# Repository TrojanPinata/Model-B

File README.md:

<div align="center">

# Model-B

### A 75% keyboard based on the RP2040 MCU with hotswappable switches, OLED display, and rotary encoder.

The Model-B is the second keyboard I've developed and aims to be the direct successor to the [Model-K](https://github.com/TrojanPinata/Model-K-Pico). I made this with the intention to develop a hotswappable keyboard which uses SMD components in order to reduce soldering overhead and learn microcontroller hardware development. The case is clear acrylic with a delrin switchplate and holds a eleven degree angle, and is reasonably heavy - a much more complete feel compared to the Model-K. 

See [what_is_this.md](what_is_this.md) for some info regarding why I made this and some of the specifics for getting setup.

## Features

<div align="left">

* 75% layout
* Hotswappable switches
* Primarily SMD PCB
* Completely laster cut housing
* 128x32 OLED display
* Chip viewing window

</div>

### Photography by [Kobe Brian!](https://www.kobebrian.com/)

</div>

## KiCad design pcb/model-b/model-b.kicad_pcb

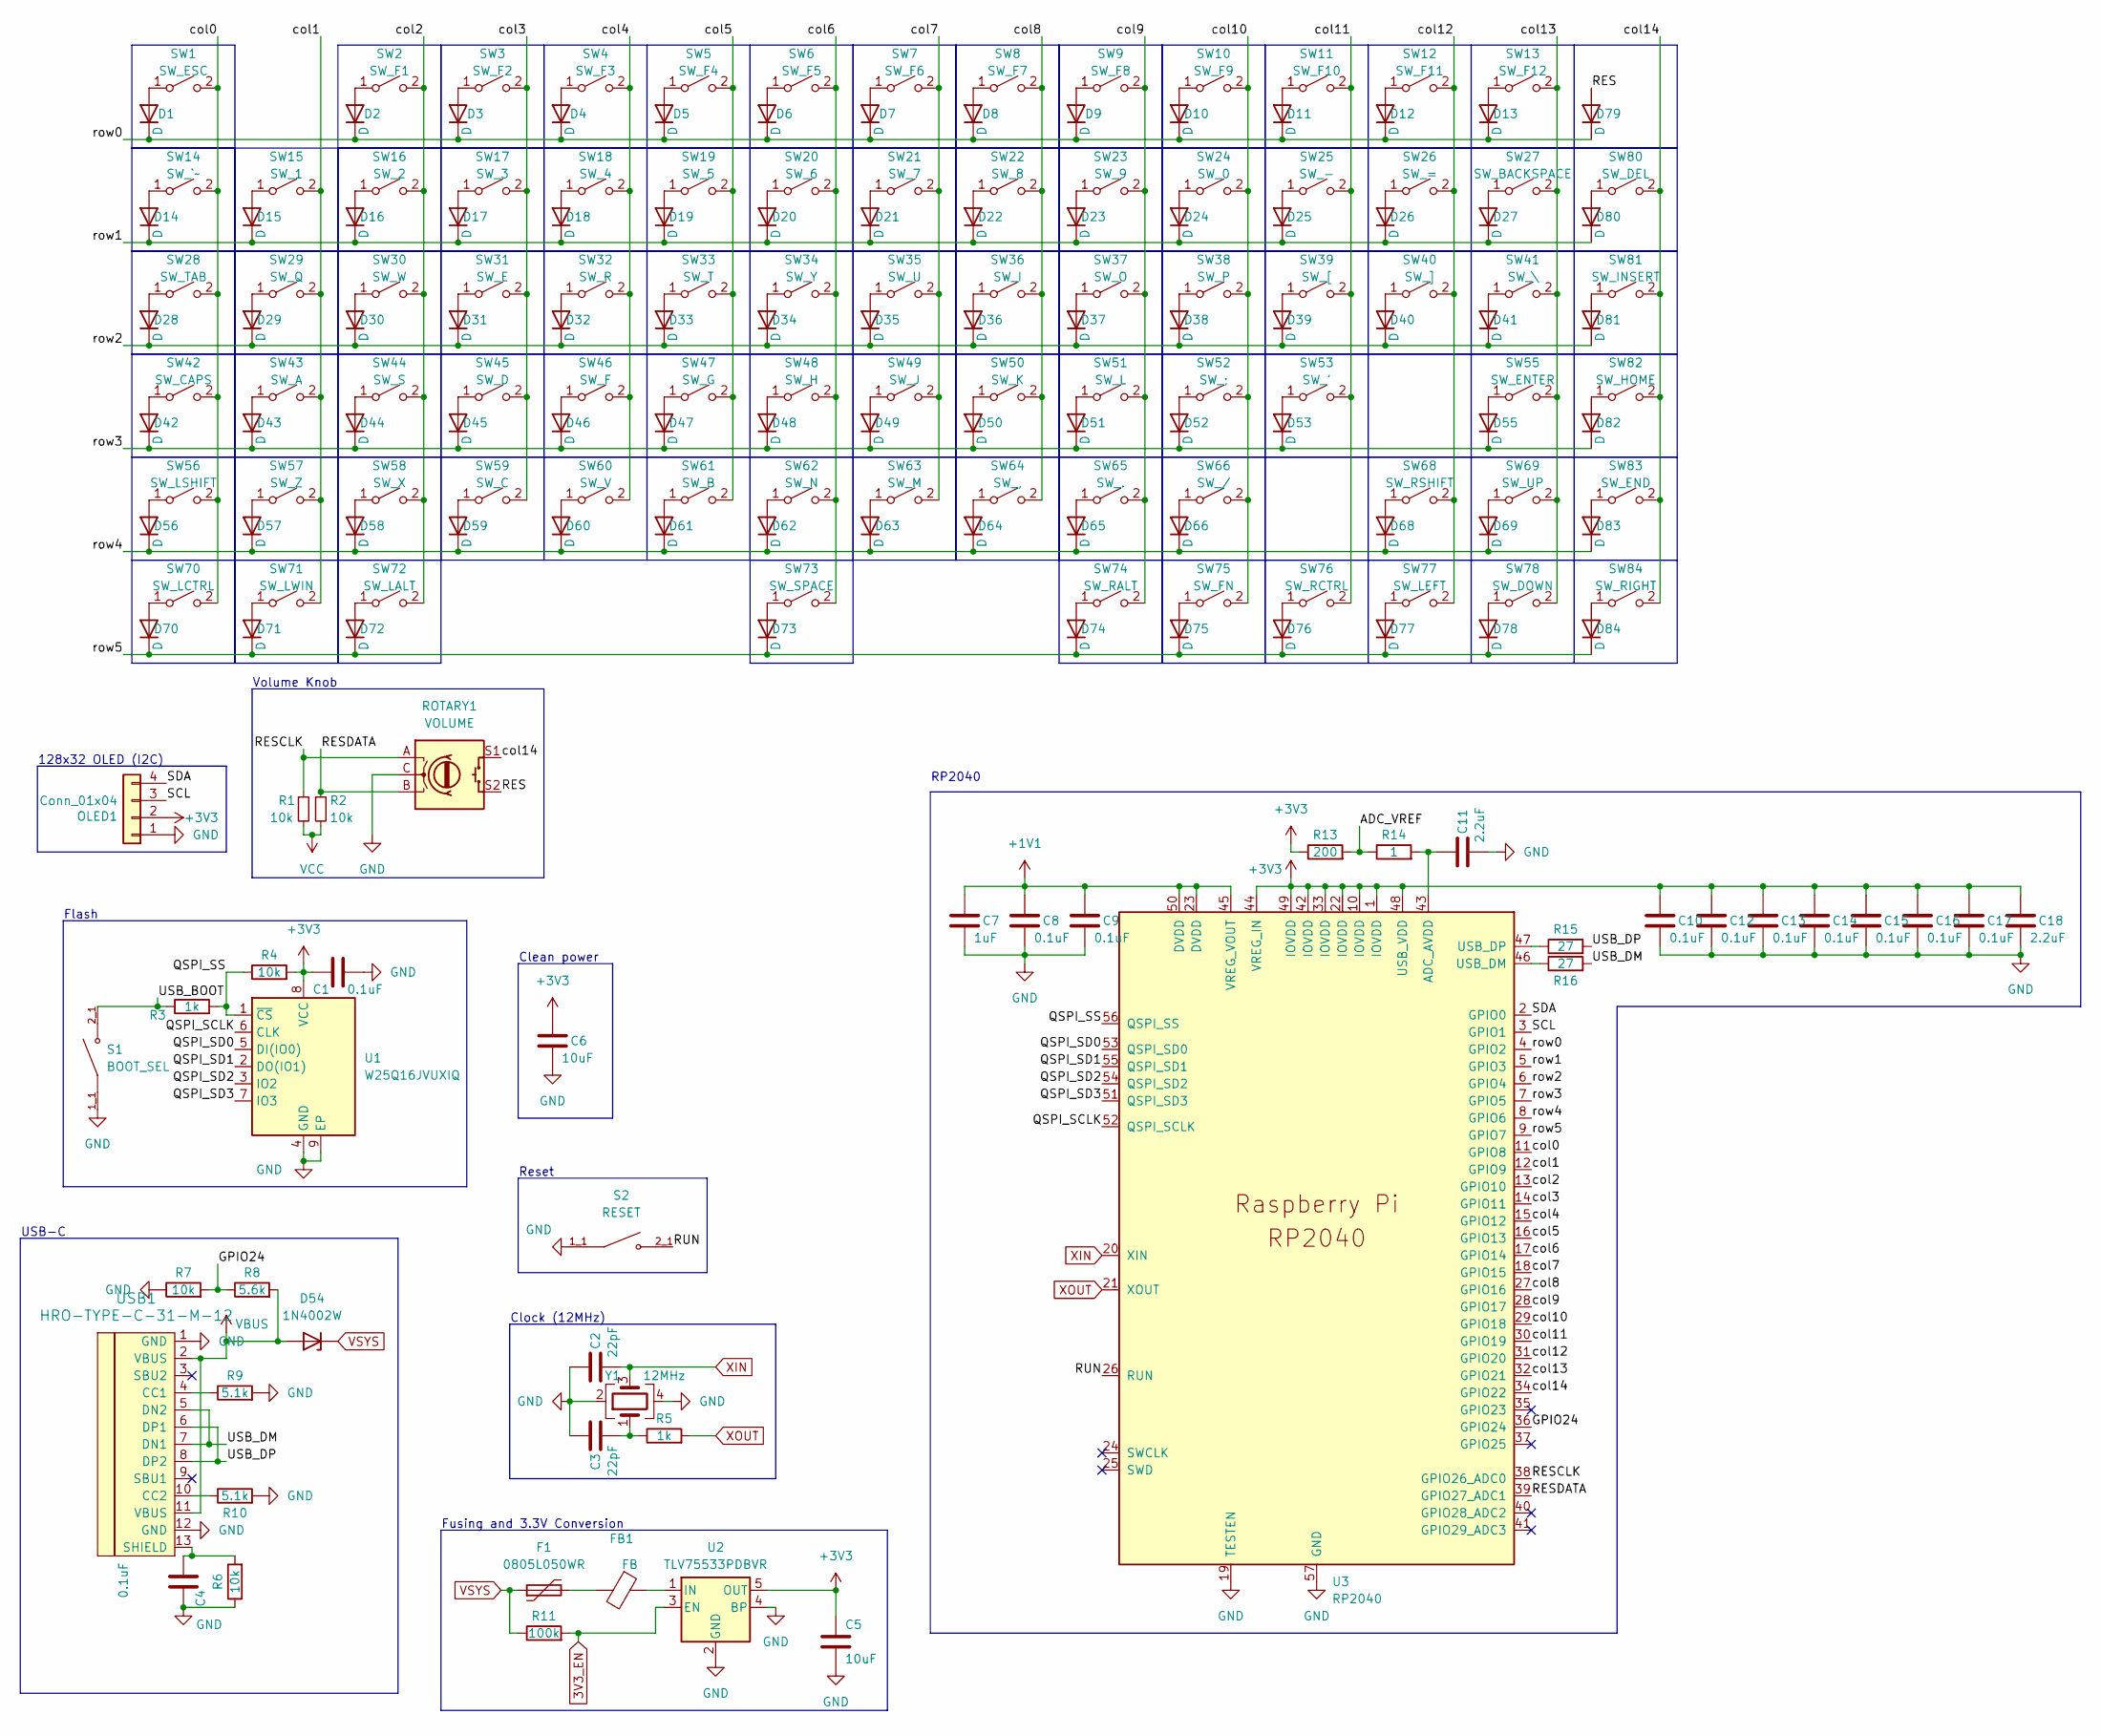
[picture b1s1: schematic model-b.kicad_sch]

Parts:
C1, C4, C8, C9, C10, C12, C13, C14, C15, C16, C17: 0.1uF; C_0402_1005Metric
C2, C3: 22pF; C_0402_1005Metric
C5, C6: 10uF; C_0402_1005Metric
C7: 1uF; C_0402_1005Metric
C11, C18: 2.2uF; C_0402_1005Metric
D1, D2, D3, D4, D5, D6, D7, D8, D9, D10, D11, D12, D13, D14, D15, D16, D17, D18, D19, D20, D21, D22, D23, D24, D25, D26, D27, D28, D29, D30, D31, D32, D33, D34, D35, D36, D37, D38, D39, D40, D41, D42, D43, D44, D45, D46, D47, D48, D49, D50, D51, D52, D53, D55, D56, D57, D58, D59, D60, D61, D62, D63, D64, D65, D66, D68, D69, D70, D71, D72, D73, D74, D75, D76, D77, D78, D79, D80, D81, D82, D83, D84: D; D_0402_1005Metric
D54: 1N4002W; D_SOD-123
F1: 0805L050WR; Fuse_0805_2012Metric
FB1: FB; R_0402_1005Metric
OLED1: Conn_01x04; PinSocket_1x04_P2.54mm_Vertical
R1, R2, R4, R6, R7: 10k; R_0402_1005Metric
R3, R5: 1k; R_0402_1005Metric
R8: 5.6k; R_0402_1005Metric
R9, R10: 5.1k; R_0402_1005Metric
R11: 100k; R_0402_1005Metric
R13: 200; R_0402_1005Metric
R14: 1; R_0402_1005Metric
R15, R16: 27; R_0402_1005Metric
ROTARY1: VOLUME; RotaryEncoder_Alps_EC11E-Switch_Vertical_H20mm_CircularMoun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
S1: BOOT_SEL; SW_EVQ-P7A01P; PARTREV 2022.4
S2: RESET; SW_EVQ-P7A01P; PARTREV 2022.4
SW1: SW_ESC; MXOnly-1U-Hotswap
SW2: SW_F1; MXOnly-1U-Hotswap
SW3: SW_F2; MXOnly-1U-Hotswap
SW4: SW_F3; MXOnly-1U-Hotswap
SW5: SW_F4; MXOnly-1U-Hotswap
SW6: SW_F5; MXOnly-1U-Hotswap
SW7: SW_F6; MXOnly-1U-Hotswap
SW8: SW_F7; MXOnly-1U-Hotswap
SW9: SW_F8; MXOnly-1U-Hotswap
SW10: SW_F9; MXOnly-1U-Hotswap
SW11: SW_F10; MXOnly-1U-Hotswap
SW12: SW_F11; MXOnly-1U-Hotswap
SW13: SW_F12; MXOnly-1U-Hotswap
SW14: SW_`~; MXOnly-1U-Hotswap
SW15: SW_1; MXOnly-1U-Hotswap
SW16: SW_2; MXOnly-1U-Hotswap
SW17: SW_3; MXOnly-1U-Hotswap
SW18: SW_4; MXOnly-1U-Hotswap
SW19: SW_5; MXOnly-1U-Hotswap
SW20: SW_6; MXOnly-1U-Hotswap
SW21: SW_7; MXOnly-1U-Hotswap
SW22: SW_8; MXOnly-1U-Hotswap
SW23: SW_9; MXOnly-1U-Hotswap
SW24: SW_0; MXOnly-1U-Hotswap
SW25: SW_-; MXOnly-1U-Hotswap
SW26: SW_=; MXOnly-1U-Hotswap
SW27: SW_BACKSPACE; MXOnly-2U-Hotswap
SW28: SW_TAB; MXOnly-1.5U-Hotswap
SW29: SW_Q; MXOnly-1U-Hotswap
SW30: SW_W; MXOnly-1U-Hotswap
SW31: SW_E; MXOnly-1U-Hotswap
SW32: SW_R; MXOnly-1U-Hotswap
SW33: SW_T; MXOnly-1U-Hotswap
SW34: SW_Y; MXOnly-1U-Hotswap
SW35: SW_U; MXOnly-1U-Hotswap
SW36: SW_I; MXOnly-1U-Hotswap
SW37: SW_O; MXOnly-1U-Hotswap
SW38: SW_P; MXOnly-1U-Hotswap
SW39: SW_[; MXOnly-1U-Hotswap
SW40: SW_]; MXOnly-1U-Hotswap
SW41: SW_\; MXOnly-1.5U-Hotswap
SW42: SW_CAPS; MXOnly-1.75U-Hotswap
SW43: SW_A; MXOnly-1U-Hotswap
SW44: SW_S; MXOnly-1U-Hotswap
SW45: SW_D; MXOnly-1U-Hotswap
SW46: SW_F; MXOnly-1U-Hotswap
SW47: SW_G; MXOnly-1U-Hotswap
SW48: SW_H; MXOnly-1U-Hotswap
SW49: SW_J; MXOnly-1U-Hotswap
SW50: SW_K; MXOnly-1U-Hotswap
SW51: SW_L; MXOnly-1U-Hotswap
SW52: SW_;; MXOnly-1U-Hotswap
SW53: SW_'; MXOnly-1U-Hotswap
SW55: SW_ENTER; MXOnly-2.25U-Hotswap
SW56: SW_LSHIFT; MXOnly-2.25U-Hotswap
SW57: SW_Z; MXOnly-1U-Hotswap
SW58: SW_X; MXOnly-1U-Hotswap
SW59: SW_C; MXOnly-1U-Hotswap
SW60: SW_V; MXOnly-1U-Hotswap
SW61: SW_B; MXOnly-1U-Hotswap
SW62: SW_N; MXOnly-1U-Hotswap
SW63: SW_M; MXOnly-1U-Hotswap
SW64: SW_,; MXOnly-1U-Hotswap
SW65: SW_.; MXOnly-1U-Hotswap
SW66: SW_/; MXOnly-1U-Hotswap
SW68: SW_RSHIFT; MXOnly-1.75U-Hotswap
SW69: SW_UP; MXOnly-1U-Hotswap
SW70: SW_LCTRL; MXOnly-1.25U-Hotswap
SW71: SW_LWIN; MXOnly-1.25U-Hotswap
SW72: SW_LALT; MXOnly-1.25U-Hotswap
SW73: SW_SPACE; MXOnly-6.25U-Hotswap
SW74: SW_RALT; MXOnly-1U-Hotswap
SW75: SW_FN; MXOnly-1U-Hotswap
SW76: SW_RCTRL; MXOnly-1U-Hotswap
SW77: SW_LEFT; MXOnly-1U-Hotswap
SW78: SW_DOWN; MXOnly-1U-Hotswap
SW80: SW_DEL; MXOnly-1U-Hotswap
SW81: SW_INSERT; MXOnly-1U-Hotswap
SW82: SW_HOME; MXOnly-1U-Hotswap
SW83: SW_END; MXOnly-1U-Hotswap
SW84: SW_RIGHT; MXOnly-1U-Hotswap
U1: W25Q16JVUXIQ; SON-8-1EP_3x2mm_P0.5mm_EP1.4x1.6mm
U2: TLV75533PDBVR; SOT-23-5
U3: RP2040; RP2040-QFN-56
USB1: HRO-TYPE-C-31-M-12
Y1: 12MHz; Crystal_SMD_3225-4Pin_3.2x2.5mm

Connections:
3V3_EN: R11.2, U2.3 (EN)
+1V1: C7.1, C8.1, C9.1, U3.23 (DVDD), U3.45 (VREG_VOUT), U3.50 (DVDD)
+3V3: C1.2, C5.1, C6.1, C10.1, C12.1, C13.1, C14.1, C15.1, C16.1, C17.1, C18.1, OLED1.2, R4.2, R13.1, U1.8 (VCC), U2.5 (OUT), U3.1 (IOVDD), U3.10 (IOVDD), U3.22 (IOVDD), U3.33 (IOVDD), U3.42 (IOVDD), U3.44 (VREG_IN), U3.48 (USB_VDD), U3.49 (IOVDD)
/ADC_VREF: R13.2, R14.1
/GPIO24: R7.2, R8.1, U3.36 (GPIO24)
/QSPI_SCLK: U1.6 (CLK), U3.52 (QSPI_SCLK)
/QSPI_SD0: U1.5 (DI(IO0)), U3.53 (QSPI_SD0)
/QSPI_SD1: U1.2 (DO(IO1)), U3.55 (QSPI_SD1)
/QSPI_SD2: U1.3 (IO2), U3.54 (QSPI_SD2)
/QSPI_SD3: U1.7 (IO3), U3.51 (QSPI_SD3)
/QSPI_SS: R3.2, R4.1, U1.1 (~CS), U3.56 (QSPI_SS)
/RES: D79.2 (A), ROTARY1.S2
/RESCLK: R1.1, ROTARY1.A, U3.38 (GPIO26_ADC0)
/RESDATA: R2.1, ROTARY1.B, U3.39 (GPIO27_ADC1)
/RUN: S2.2_1, U3.26 (RUN)
/SCL: OLED1.3, U3.3 (GPIO1)
/SDA: OLED1.4, U3.2 (GPIO0)
/USB_BOOT: R3.1, S1.2_1
/USB_DM: R16.2, USB1.5 (DN2), USB1.7 (DN1)
/USB_DP: R15.2, USB1.6 (DP1), USB1.8 (DP2)
/col0: SW1.2 (B), SW14.2 (B), SW28.2 (B), SW42.2 (B), SW56.2 (B), SW70.2 (B), U3.11 (GPIO8)
/col1: SW15.2 (B), SW29.2 (B), SW43.2 (B), SW57.2 (B), SW71.2 (B), U3.12 (GPIO9)
/col2: SW2.2 (B), SW16.2 (B), SW30.2 (B), SW44.2 (B), SW58.2 (B), SW72.2 (B), U3.13 (GPIO10)
/col3: SW3.2 (B), SW17.2 (B), SW31.2 (B), SW45.2 (B), SW59.2 (B), U3.14 (GPIO11)
/col4: SW4.2 (B), SW18.2 (B), SW32.2 (B), SW46.2 (B), SW60.2 (B), U3.15 (GPIO12)
/col5: SW5.2 (B), SW19.2 (B), SW33.2 (B), SW47.2 (B), SW61.2 (B), U3.16 (GPIO13)
/col6: SW6.2 (B), SW20.2 (B), SW34.2 (B), SW48.2 (B), SW62.2 (B), SW73.2 (B), U3.17 (GPIO14)
/col7: SW7.2 (B), SW21.2 (B), SW35.2 (B), SW49.2 (B), SW63.2 (B), U3.18 (GPIO15)
/col8: SW8.2 (B), SW22.2 (B), SW36.2 (B), SW50.2 (B), SW64.2 (B), U3.27 (GPIO16)
/col9: SW9.2 (B), SW23.2 (B), SW37.2 (B), SW51.2 (B), SW65.2 (B), SW74.2 (B), U3.28 (GPIO17)
/col10: SW10.2 (B), SW24.2 (B), SW38.2 (B), SW52.2 (B), SW66.2 (B), SW75.2 (B), U3.29 (GPIO18)
/col11: SW11.2 (B), SW25.2 (B), SW39.2 (B), SW53.2 (B), SW76.2 (B), U3.30 (GPIO19)
/col12: SW12.2 (B), SW26.2 (B), SW40.2 (B), SW68.2 (B), SW77.2 (B), U3.31 (GPIO20)
/col13: SW13.2 (B), SW27.2 (B), SW41.2 (B), SW55.2 (B), SW69.2 (B), SW78.2 (B), U3.32 (GPIO21)
/col14: ROTARY1.S1, SW80.2 (B), SW81.2 (B), SW82.2 (B), SW83.2 (B), SW84.2 (B), U3.34 (GPIO22)
/row0: D1.1 (K), D2.1 (K), D3.1 (K), D4.1 (K), D5.1 (K), D6.1 (K), D7.1 (K), D8.1 (K), D9.1 (K), D10.1 (K), D11.1 (K), D12.1 (K), D13.1 (K), D79.1 (K), U3.4 (GPIO2)
/row1: D14.1 (K), D15.1 (K), D16.1 (K), D17.1 (K), D18.1 (K), D19.1 (K), D20.1 (K), D21.1 (K), D22.1 (K), D23.1 (K), D24.1 (K), D25.1 (K), D26.1 (K), D27.1 (K), D80.1 (K), U3.5 (GPIO3)
/row2: D28.1 (K), D29.1 (K), D30.1 (K), D31.1 (K), D32.1 (K), D33.1 (K), D34.1 (K), D35.1 (K), D36.1 (K), D37.1 (K), D38.1 (K), D39.1 (K), D40.1 (K), D41.1 (K), D81.1 (K), U3.6 (GPIO4)
/row3: D42.1 (K), D43.1 (K), D44.1 (K), D45.1 (K), D46.1 (K), D47.1 (K), D48.1 (K), D49.1 (K), D50.1 (K), D51.1 (K), D52.1 (K), D53.1 (K), D55.1 (K), D82.1 (K), U3.7 (GPIO5)
/row4: D56.1 (K), D57.1 (K), D58.1 (K), D59.1 (K), D60.1 (K), D61.1 (K), D62.1 (K), D63.1 (K), D64.1 (K), D65.1 (K), D66.1 (K), D68.1 (K), D69.1 (K), D83.1 (K), U3.8 (GPIO6)
/row5: D70.1 (K), D71.1 (K), D72.1 (K), D73.1 (K), D74.1 (K), D75.1 (K), D76.1 (K), D77.1 (K), D78.1 (K), D84.1 (K), U3.9 (GPIO7)
GND: C1.1, C2.1, C3.2, C4.2, C5.2, C6.2, C7.2, C8.2, C9.2, C10.2, C11.2, C12.2, C13.2, C14.2, C15.2, C16.2, C17.2, C18.2, OLED1.1, R6.1, R7.1, R9.2, R10.2, ROTARY1.C, S1.1_1, S2.1_1, U1.4 (GND), U1.9 (EP), U2.2 (GND), U2.4 (BP), U3.19 (TESTEN), U3.57 (GND), USB1.1 (GND), USB1.12 (GND), Y1.2, Y1.4
unnamed: C3.1, R5.1, Y1.1
unnamed: D1.2 (A), SW1.1 (A)
unnamed: D2.2 (A), SW2.1 (A)
unnamed: D3.2 (A), SW3.1 (A)
unnamed: D4.2 (A), SW4.1 (A)
unnamed: D5.2 (A), SW5.1 (A)
unnamed: D6.2 (A), SW6.1 (A)
unnamed: D7.2 (A), SW7.1 (A)
unnamed: D8.2 (A), SW8.1 (A)
unnamed: D9.2 (A), SW9.1 (A)
unnamed: D10.2 (A), SW10.1 (A)
unnamed: D11.2 (A), SW11.1 (A)
unnamed: D12.2 (A), SW12.1 (A)
unnamed: D13.2 (A), SW13.1 (A)
unnamed: D14.2 (A), SW14.1 (A)
unnamed: D15.2 (A), SW15.1 (A)
unnamed: D16.2 (A), SW16.1 (A)
unnamed: D17.2 (A), SW17.1 (A)
unnamed: D18.2 (A), SW18.1 (A)
unnamed: D19.2 (A), SW19.1 (A)
unnamed: D20.2 (A), SW20.1 (A)
unnamed: D21.2 (A), SW21.1 (A)
unnamed: D22.2 (A), SW22.1 (A)
unnamed: D23.2 (A), SW23.1 (A)
unnamed: D24.2 (A), SW24.1 (A)
unnamed: D25.2 (A), SW25.1 (A)
unnamed: D26.2 (A), SW26.1 (A)
unnamed: D27.2 (A), SW27.1 (A)
unnamed: D28.2 (A), SW28.1 (A)
unnamed: D29.2 (A), SW29.1 (A)
unnamed: D30.2 (A), SW30.1 (A)
unnamed: D31.2 (A), SW31.1 (A)
unnamed: D32.2 (A), SW32.1 (A)
unnamed: D33.2 (A), SW33.1 (A)
unnamed: D34.2 (A), SW34.1 (A)
unnamed: D35.2 (A), SW35.1 (A)
unnamed: D36.2 (A), SW36.1 (A)
unnamed: D37.2 (A), SW37.1 (A)
unnamed: D38.2 (A), SW38.1 (A)
unnamed: D39.2 (A), SW39.1 (A)
unnamed: D40.2 (A), SW40.1 (A)
unnamed: D41.2 (A), SW41.1 (A)
unnamed: D42.2 (A), SW42.1 (A)
unnamed: D43.2 (A), SW43.1 (A)
unnamed: D44.2 (A), SW44.1 (A)
unnamed: D45.2 (A), SW45.1 (A)
unnamed: D46.2 (A), SW46.1 (A)
unnamed: D47.2 (A), SW47.1 (A)
unnamed: D48.2 (A), SW48.1 (A)
unnamed: D49.2 (A), SW49.1 (A)
unnamed: D50.2 (A), SW50.1 (A)
unnamed: D51.2 (A), SW51.1 (A)
unnamed: D52.2 (A), SW52.1 (A)
unnamed: D53.2 (A), SW53.1 (A)
unnamed: D55.2 (A), SW55.1 (A)
unnamed: D56.2 (A), SW56.1 (A)
unnamed: D57.2 (A), SW57.1 (A)
unnamed: D58.2 (A), SW58.1 (A)
unnamed: D59.2 (A), SW59.1 (A)
unnamed: D60.2 (A), SW60.1 (A)
unnamed: D61.2 (A), SW61.1 (A)
unnamed: D62.2 (A), SW62.1 (A)
unnamed: D63.2 (A), SW63.1 (A)
unnamed: D64.2 (A), SW64.1 (A)
unnamed: D65.2 (A), SW65.1 (A)
unnamed: D66.2 (A), SW66.1 (A)
unnamed: D68.2 (A), SW68.1 (A)
unnamed: D69.2 (A), SW69.1 (A)
unnamed: D70.2 (A), SW70.1 (A)
unnamed: D71.2 (A), SW71.1 (A)
unnamed: D72.2 (A), SW72.1 (A)
unnamed: D73.2 (A), SW73.1 (A)
unnamed: D74.2 (A), SW74.1 (A)
unnamed: D75.2 (A), SW75.1 (A)
unnamed: D76.2 (A), SW76.1 (A)
unnamed: D77.2 (A), SW77.1 (A)
unnamed: D78.2 (A), SW78.1 (A)
unnamed: D80.2 (A), SW80.1 (A)
unnamed: D81.2 (A), SW81.1 (A)
unnamed: D82.2 (A), SW82.1 (A)
unnamed: D83.2 (A), SW83.1 (A)
unnamed: D84.2 (A), SW84.1 (A)
unnamed: F1.2, FB1.2
unnamed: FB1.1, U2.1 (IN)
unnamed: C11.1, R14.2, U3.43 (ADC_AVDD)
unnamed: R16.1, U3.46 (USB_DM)
unnamed: R15.1, U3.47 (USB_DP)
unnamed: R9.1, USB1.4 (CC1)
unnamed: R10.1, USB1.10 (CC2)
unnamed: C4.1, R6.2, USB1.13 (SHIELD)
VBUS: D54.2 (A), R8.2, USB1.2 (VBUS), USB1.11 (VBUS)
VCC: R1.2, R2.2
VSYS: D54.1 (K), F1.1, R11.1
XIN: C2.2, U3.20 (XIN), Y1.3
XOUT: R5.2, U3.21 (XOUT)

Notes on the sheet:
128x32 OLED (I2C)
Clean power
USB-C
Flash
Fusing and 3.3V Conversion
Volume Knob
Reset
Clock (12MHz)
RP2040

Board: 2 copper layers, 208 parts (0 on the bottom side), 137 nets, no tracks yet.

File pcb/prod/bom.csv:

Designator,Footprint,Quantity,Value,LCSC Part #
"C1, C10, C12, C13, C14, C15, C16, C17, C4, C8, C9",0402,11,0.1uF,C1525
"C11, C18",0402,2,2.2uF,C12530
"C2, C3",0402,2,20pF,C1554
"C5, C6",0402,2,10uF,C15525
C7,0402,1,1uF,C52923
"D1, D10, D11, D12, D13, D14, D15, D16, D17, D18, D19, D2, D20, D21, D22, D23, D24, D25, D26, D27, D28, D29, D3, D30, D31, D32, D33, D34, D35, D36, D37, D38, D39, D4, D40, D41, D42, D43, D44, D45, D46, D47, D48, D49, D5, D50, D51, D52, D53, D55, D56, D57, D58, D59, D6, D60, D61, D62, D63, D64, D65, D66, D67, D68, D69, D7, D70, D71, D72, D73, D74, D75, D76, D77, D78, D79, D8, D80, D81, D82, D83, D84, D9",D_SOD-123,83,D,C7420318
D54,D_SOD-123,1,1N4002W,C169542
F1,0805,1,0805L050WR,C207022
FB1,0402,1,FB,C160973
"R1, R2, R4, R6, R7",0402,5,10k,C25744
"R10, R9",0402,2,5.1k,C25905
R11,0402,1,100k,C25741
R13,0402,1,200,C25087
R14,0402,1,1,C25086
"R15, R16",0402,2,27,C25100
"R3, R5",0402,2,1k,C11702
R8,0402,1,5.6k,C25908
S1,SW_EVQ-P7A01P,1,BOOT_SEL,C485515
S2,SW_EVQ-P7A01P,1,RESET,C485515
U1,SON-8-1EP_3x2mm_P0.5mm_EP1.4x1.6mm,1,W25Q16JVUXIQ,C2843335
U2,SOT-23-5,1,TLV75533PDBVR,C404027
U3,RP2040-QFN-56,1,RP2040,C2040
USB1,HRO-TYPE-C-31-M-12,1,HRO-TYPE-C-31-M-12,C165948
Y1,Crystal_SMD_3225-4Pin_3.2x2.5mm,1,12MHz,C9002

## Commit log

2024-06-19 Schematic and keymap done, routing in progress
2024-06-20 finished pcb (probably)
2024-07-03 fixed diodes to be SOD-123 and added case files
2024-07-05 added step files - todo: fix open_liner and switchplate
2024-07-07 firmware in progress, case design being finalized, pcb fixed, bom in progress
2024-07-07 quick fix for looping through screens
2024-07-27 Finished case, minor changes to PCB, laser cutting files prepped
2024-07-31 Added decal to visualize PCB window and validate holes
2024-09-14 PCBs ordered, pray they come without errors
2024-09-26 PCBs tested and good, soldering in progress. FW updated to add encoder. Case files in QA, almost ready to order
2024-10-04 fixed laser cutting files and reordered
2024-11-05 updated readme and added descriptor document
2024-11-05 fixed image centering
2024-11-05 fixing images (yes again)
2024-11-08 updated gitignore
2024-11-13 add keymap to readme
2024-11-28 Updated firmware to include three extra screens, updated README with photos and better layout
2024-12-21 updated firmware and added to qmk_firmware repo
